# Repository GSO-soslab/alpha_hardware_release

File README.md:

## ALPHA HARDWARE RELEASE
This repository provides design files for ALPHA AUV hardware.
- `Electronics` folder contains KiCad PCB files, documentations and guides.
- `CAD` folder contains CAD files for the mechanical parts.

**License: CERN-OHL-S-2.0**

**Funding:** NSF Award #2221676, #2238168 and #2154901

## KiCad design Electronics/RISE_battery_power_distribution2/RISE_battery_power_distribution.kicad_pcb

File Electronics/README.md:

# ALPHA Hardware Repositority

The ALPHA Eletronics Hardware design is released under  [CERN-OHL-S-2.0](https://ohwr.org/cern_ohl_s_v2.txt) Licence
## **Introduction**

The most recent update:

- `sbc_hat` is a expansion board for single-board computers. It contains 8 RS232 ports (4 selectable between UART and RS232), 2 I2C buses, 2 ADC channels, and 5 direct GPIO connections. PDF schematics is available [here](https://github.com/GSO-soslab/alpha_hardware_release/blob/main/Electronics/doc/Schematics/sbc_hat.pdf)

- `thruster_driver` is a breakout board for MCU (MicroMod RP2040). This board is designed for interface with ESCs to control the thruster and servos. The voltage sensing capability is available (using a voltage devider) to monitoring the voltage to the thrusters. Communication ports are I2C, RS232 and RS485. Two additional GPIO is available for Digital Output fucntion. PDF schematics is available [here](https://github.com/GSO-soslab/alpha_hardware_release/blob/main/Electronics/doc/Schematics/thruster_driver.pdf)
 
- `Battery management` is a breakout board that uses diodes to allow battery pack parallization upto 4 packs. **IMPORTANT: You cannot charge batter packs from the Vout port on the board**

- `alpha_power_distribution_board` is a breakout board for distributing power sources for different devices on the ALPHA. You can plug in Pololu DC/DC circuit on the board with a 90 degree angled pin headers. A PDF schematics is available [here](https://github.com/GSO-soslab/alpha_hardware_release/blob/main/Electronics/doc/Schematics/alpha_power_distribution.pdf)

The detailed hardware information is available in the following links for users.
- [PI setup guide](https://github.com/GSO-soslab/alpha_hardware_release/blob/main/Electronics/doc/PI_setup_guide.md): This document provide information on how to configure the chips on the sbc_hat PBC.

- [`sbc_hat`](https://github.com/GSO-soslab/alpha_hardware_release/blob/main/Electronics/doc/SBC_HAT.md)

- [`thruster_driver`](https://github.com/GSO-soslab/alpha_hardware_release/blob/main/Electronics/doc/Thruster_driver.md)

- [`alpha_power_distribution_board`](https://github.com/GSO-soslab/alpha_hardware_release/blob/main/Electronics/doc/Alpha_power_distribution.md).

- [`Battery management`](https://github.com/GSO-soslab/alpha_hardware_release/blob/main/Electronics/doc/Battery_management.md)

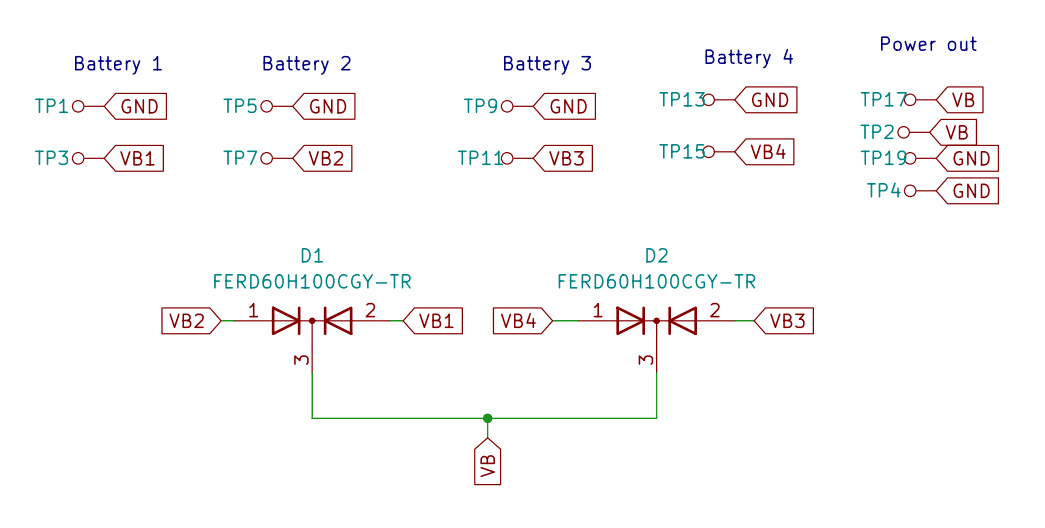
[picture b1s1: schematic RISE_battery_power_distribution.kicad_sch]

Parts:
D1, D2: FERD60H100CGY-TR; STPS41L60CG-TR
TP1, TP2, TP3, TP4, TP5, TP7, TP9, TP11, TP13, TP15, TP17, TP19: 5016; Test_Point_3.43x1.78mm; MPN 5016; Digi-Key_PN 36-5016CT-ND

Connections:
GND: TP1.1, TP4.1, TP5.1, TP9.1, TP13.1, TP19.1
VB: D1.3 (K), D2.3 (K), TP2.1, TP17.1
VB1: D1.2 (A), TP3.1
VB2: D1.1 (A), TP7.1
VB3: D2.2 (A), TP11.1
VB4: D2.1 (A), TP15.1

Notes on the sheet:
Battery 3
Battery 2
Battery 1
Battery 4
Power out

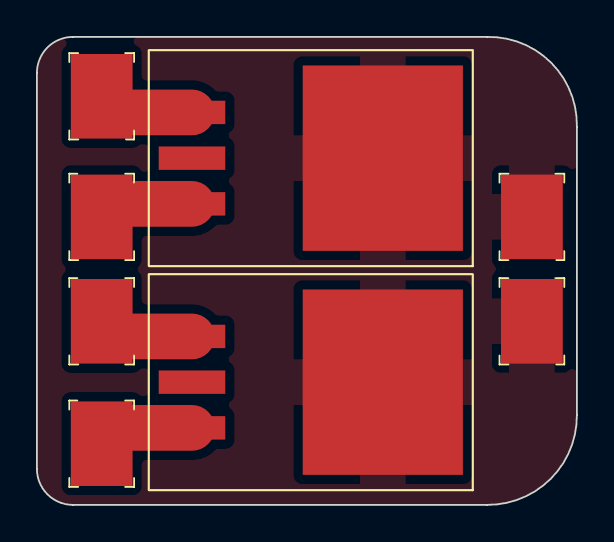
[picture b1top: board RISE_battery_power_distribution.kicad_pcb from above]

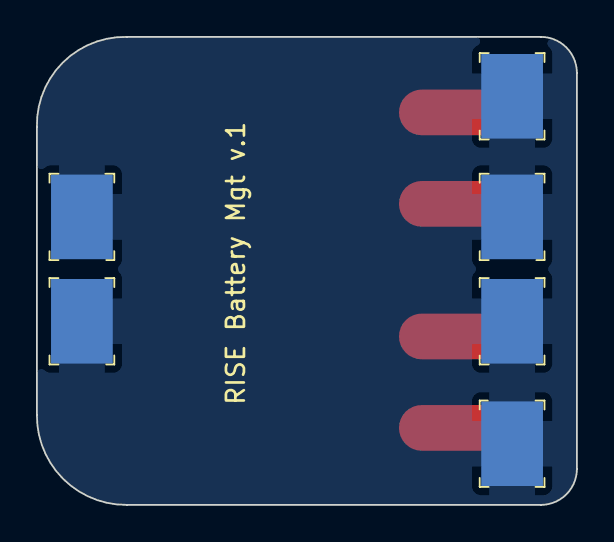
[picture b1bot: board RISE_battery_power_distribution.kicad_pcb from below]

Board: 2 copper layers, 30.0 x 26.0 mm, 14 parts (6 on the bottom side), 6 nets.

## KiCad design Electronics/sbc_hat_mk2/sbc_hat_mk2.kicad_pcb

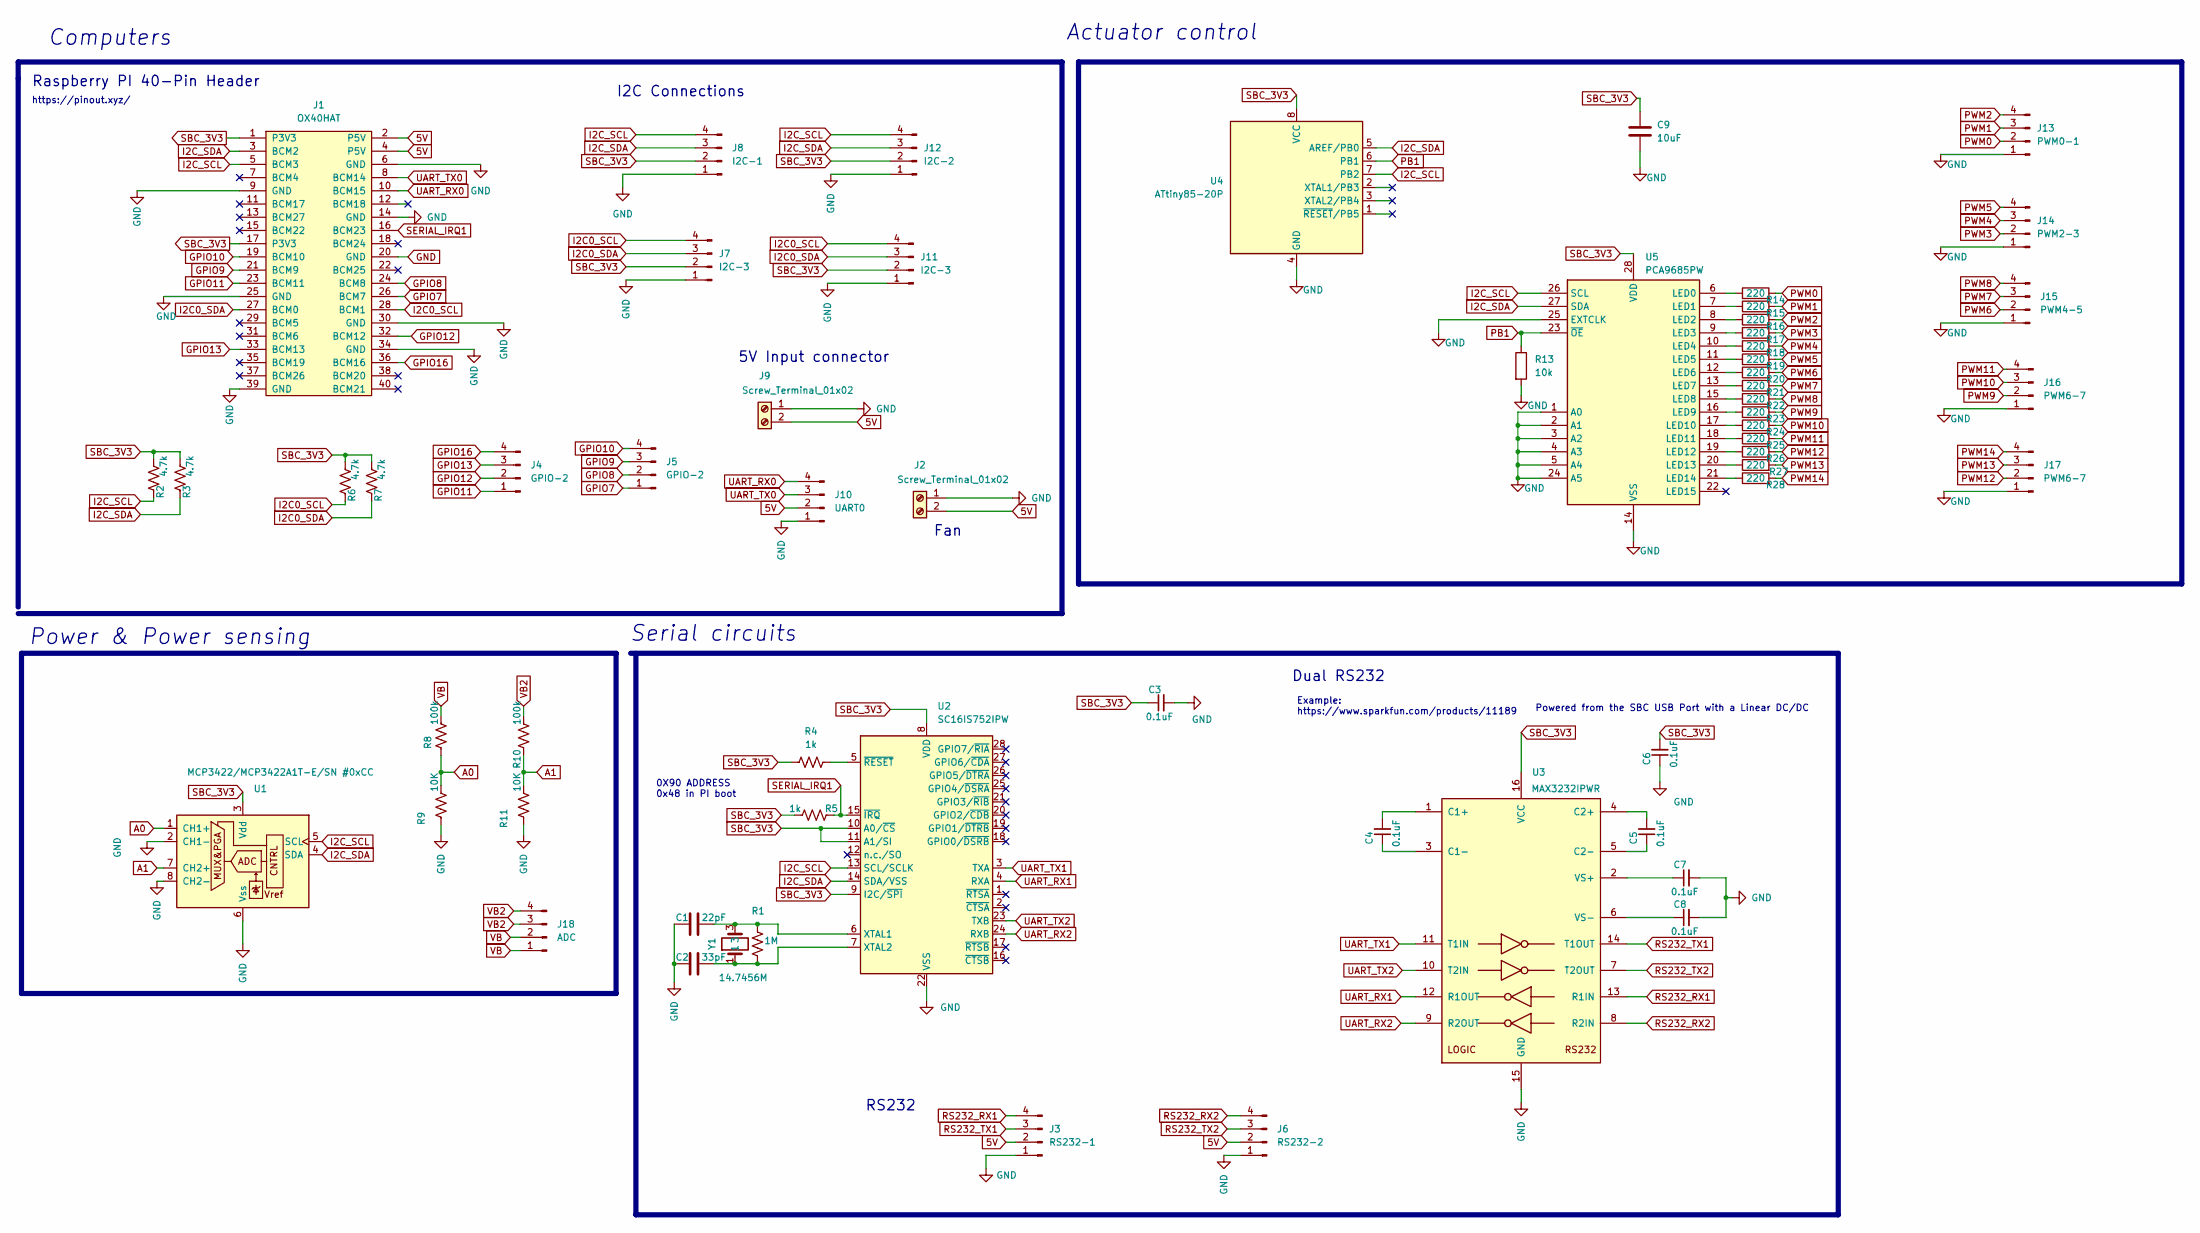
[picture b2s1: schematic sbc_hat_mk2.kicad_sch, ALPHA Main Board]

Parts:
C1: 22pF; C_0805_2012Metric; Manufacturer_Part_Number 08055J220FBTTR; Digikey Part Number 478-11911-1-ND
C2: 33pF; C_0805_2012Metric; Manufacturer_Part_Number 600F330FT250XT; Digikey Part Number 1284-1049-1-ND
C3, C4, C5, C6, C7, C8: 0.1uF; C_0805_2012Metric; Manufacturer_Part_Number 0805ZC104JAT2A; Digikey Part Number 478-11627-1-ND
C9: 10uF; C_0805_2012Metric
J1: OX40HAT; PinSocket_2x20_P2.54mm_Vertical; Mouser Part Number 474-PRT-14017
J2, J9: Screw_Terminal_01x02; TerminalBlock_Phoenix_MPT-0,5-2-2.54_1x02_P2.54mm_Horizontal; Manufacturer_Part_Number 1725656; Mouser Part Number 651-1725656
J3: RS232-1; JST_SH_BM04B-SRSS-TB_1x04-1MP_P1.00mm_Vertical; Manufacturer_Part_Number 4328; Digikey Part Number 1528-4328-ND
J4, J5: GPIO-2; JST_SH_BM04B-SRSS-TB_1x04-1MP_P1.00mm_Vertical; Manufacturer_Part_Number 4328; Digikey Part Number 1528-4328-ND
J6: RS232-2; JST_SH_BM04B-SRSS-TB_1x04-1MP_P1.00mm_Vertical; Manufacturer_Part_Number 4328; Digikey Part Number 1528-4328-ND
J7, J11: I2C-3; JST_SH_BM04B-SRSS-TB_1x04-1MP_P1.00mm_Vertical; Manufacturer_Part_Number 4328; Digikey Part Number 1528-4328-ND
J8: I2C-1; JST_SH_BM04B-SRSS-TB_1x04-1MP_P1.00mm_Vertical; Manufacturer_Part_Number 4328; Digikey Part Number 1528-4328-ND
J10: UART0; JST_SH_BM04B-SRSS-TB_1x04-1MP_P1.00mm_Vertical; Manufacturer_Part_Number 4328; Digikey Part Number 1528-4328-ND
J12: I2C-2; JST_SH_BM04B-SRSS-TB_1x04-1MP_P1.00mm_Vertical; Manufacturer_Part_Number 4328; Digikey Part Number 1528-4328-ND
J13: PWM0-1; JST_SH_BM04B-SRSS-TB_1x04-1MP_P1.00mm_Vertical; Manufacturer_Part_Number 4328; Digikey Part Number 1528-4328-ND
J14: PWM2-3; JST_SH_BM04B-SRSS-TB_1x04-1MP_P1.00mm_Vertical; Manufacturer_Part_Number 4328; Digikey Part Number 1528-4328-ND
J15: PWM4-5; JST_SH_BM04B-SRSS-TB_1x04-1MP_P1.00mm_Vertical; Manufacturer_Part_Number 4328; Digikey Part Number 1528-4328-ND
J16, J17: PWM6-7; JST_SH_BM04B-SRSS-TB_1x04-1MP_P1.00mm_Vertical; Manufacturer_Part_Number 4328; Digikey Part Number 1528-4328-ND
J18: ADC; JST_SH_BM04B-SRSS-TB_1x04-1MP_P1.00mm_Vertical; Manufacturer_Part_Number 4328; Digikey Part Number 1528-4328-ND
R1: 1M; R_0805_2012Metric; Manufacturer_Part_Number ERA-6AED105V; Mouser Part Number 667-ERA-6AED105V
R2, R3, R6, R7: 4.7k; R_0805_2012Metric; Manufacturer_Part_Number ERJ-T06J472V; Mouser Part Number 667-ERJ-T06J472V
R4, R5: 1k; R_0805_2012Metric; Manufacturer_Part_Number 1-2176092-8; Digikey Part Number A110543CT-ND
R8, R10: 100k; R_0805_2012Metric; Manufacturer_Part_Number ERA-6AEB104V; Mouser Part Number 667-ERA-6AEB104V
R9, R11: 10K; R_0805_2012Metric; Manufacturer_Part_Number ERA-6AEB104V; Mouser Part Number 667-ERA-6AEB104V
R13: 10k; R_0805_2012Metric
R14, R15, R16, R17, R18, R19, R20, R21, R22, R23, R24, R25, R26, R27, R28: 220; R_0805_2012Metric
U1: MCP3422/MCP3422A1T-E/SN #0xCC; SOIC-8-1EP_3.9x4.9mm_P1.27mm_EP2.29x3mm
U2: SC16IS752IPW; TSSOP-28_4.4x9.7mm_P0.65mm
U3: MAX3232IPWR; TSSOP-16_4.4x5mm_P0.65mm; Manufacturer_Part_Number MAX3232IPWR; Mouser Part Number 595-MAX3232IPWR
U4: ATtiny85-20P; DIP-8_W7.62mm
U5: PCA9685PW; TSSOP-28_4.4x9.7mm_P0.65mm
Y1: 14.7456M; Crystal_SMD_3225-4Pin_3.2x2.5mm

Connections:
5V: J1.2 (P5V), J1.4 (P5V), J2.2, J3.2, J6.2, J9.2, J10.2
A0: R8.2, R9.1, U1.1 (CH1+)
A1: R10.2, R11.1, U1.7 (CH2+)
GND: C1.1, C2.1, C3.2, C6.1, C7.2, C8.2, C9.2, J1.6 (GND), J1.9 (GND), J1.14 (GND), J1.20 (GND), J1.25 (GND), J1.30 (GND), J1.34 (GND), J1.39 (GND), J2.1, J3.1, J6.1, J7.1, J8.1, J9.1, J10.1, J11.1, J12.1, J13.1, J14.1, J15.1, J16.1, J17.1, R9.2, R11.2, R13.2, U1.2 (CH1-), U1.6 (Vss), U1.8 (CH2-), U2.22 (VSS), U3.15 (GND), U4.4 (GND), U5.1 (A0), U5.2 (A1), U5.3 (A2), U5.4 (A3), U5.5 (A4), U5.14 (VSS), U5.24 (A5), U5.25 (EXTCLK)
GPIO7: J1.26 (BCM7), J5.1
GPIO8: J1.24 (BCM8), J5.2
GPIO9: J1.21 (BCM9), J5.3
GPIO10: J1.19 (BCM10), J5.4
GPIO11: J1.23 (BCM11), J4.1
GPIO12: J1.32 (BCM12), J4.2
GPIO13: J1.33 (BCM13), J4.3
GPIO16: J1.36 (BCM16), J4.4
I2C0_SCL: J1.28 (BCM1), J7.4, J11.4, R6.1
I2C0_SDA: J1.27 (BCM0), J7.3, J11.3, R7.1
I2C_SCL: J1.5 (BCM3), J8.4, J12.4, R2.1, U1.5 (SCL), U2.13 (SCL/SCLK), U4.7 (PB2), U5.26 (SCL)
I2C_SDA: J1.3 (BCM2), J8.3, J12.3, R3.1, U1.4 (SDA), U2.14 (SDA/VSS), U4.5 (AREF/PB0), U5.27 (SDA)
unnamed: C1.2, R1.1, U2.6 (XTAL1), Y1.3
unnamed: C2.2, R1.2, U2.7 (XTAL2), Y1.1
unnamed: R4.2, U2.5 (~RESET)
unnamed: C4.2, U3.1 (C1+)
unnamed: C4.1, U3.3 (C1-)
unnamed: C5.2, U3.4 (C2+)
unnamed: C5.1, U3.5 (C2-)
unnamed: C7.1, U3.2 (VS+)
unnamed: C8.1, U3.6 (VS-)
unnamed: R14.1, U5.6 (LED0)
unnamed: R15.1, U5.7 (LED1)
unnamed: R16.1, U5.8 (LED2)
unnamed: R17.1, U5.9 (LED3)
unnamed: R18.1, U5.10 (LED4)
unnamed: R19.1, U5.11 (LED5)
unnamed: R20.1, U5.12 (LED6)
unnamed: R21.1, U5.13 (LED7)
unnamed: R22.1, U5.15 (LED8)
unnamed: R23.1, U5.16 (LED9)
unnamed: R24.1, U5.17 (LED10)
unnamed: R25.1, U5.18 (LED11)
unnamed: R26.1, U5.19 (LED12)
unnamed: R27.1, U5.20 (LED13)
unnamed: R28.1, U5.21 (LED14)
PB1: R13.1, U4.6 (PB1), U5.23 (~OE)
PWM0: J13.2, R14.2
PWM1: J13.3, R15.2
PWM2: J13.4, R16.2
PWM3: J14.2, R17.2
PWM4: J14.3, R18.2
PWM5: J14.4, R19.2
PWM6: J15.2, R20.2
PWM7: J15.3, R21.2
PWM8: J15.4, R22.2
PWM9: J16.2, R23.2
PWM10: J16.3, R24.2
PWM11: J16.4, R25.2
PWM12: J17.2, R26.2
PWM13: J17.3, R27.2
PWM14: J17.4, R28.2
RS232_RX1: J3.4, U3.13 (R1IN)
RS232_RX2: J6.4, U3.8 (R2IN)
RS232_TX1: J3.3, U3.14 (T1OUT)
RS232_TX2: J6.3, U3.7 (T2OUT)
SBC_3V3: C3.1, C6.2, C9.1, J1.1 (P3V3), J1.17 (P3V3), J7.2, J8.2, J11.2, J12.2, R2.2, R3.2, R4.1, R5.2, R6.2, R7.2, U1.3 (Vdd), U2.8 (VDD), U2.9 (I2C/~SPI), U2.10 (A0/~CS), U2.11 (A1/SI), U3.16 (VCC), U4.8 (VCC), U5.28 (VDD)
SERIAL_IRQ1: J1.16 (BCM23), R5.1, U2.15 (~IRQ)
UART_RX0: J1.10 (BCM15), J10.4
UART_RX1: U2.4 (RXA), U3.12 (R1OUT)
UART_RX2: U2.24 (RXB), U3.9 (R2OUT)
UART_TX0: J1.8 (BCM14), J10.3
UART_TX1: U2.3 (TXA), U3.11 (T1IN)
UART_TX2: U2.23 (TXB), U3.10 (T2IN)
VB: J18.1, J18.2, R8.1
VB2: J18.3, J18.4, R10.1

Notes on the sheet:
I2C Connections
0X90 ADDRESS 0x48 in PI boot
5V Input connector
RS232
Serial circuits
Dual RS232
Power & Power sensing
Example: https://www.sparkfun.com/products/11189
Fan
Computers
https://pinout.xyz/
Actuator control
Raspberry PI 40-Pin Header
Powered from the SBC USB Port with a Linear DC/DC

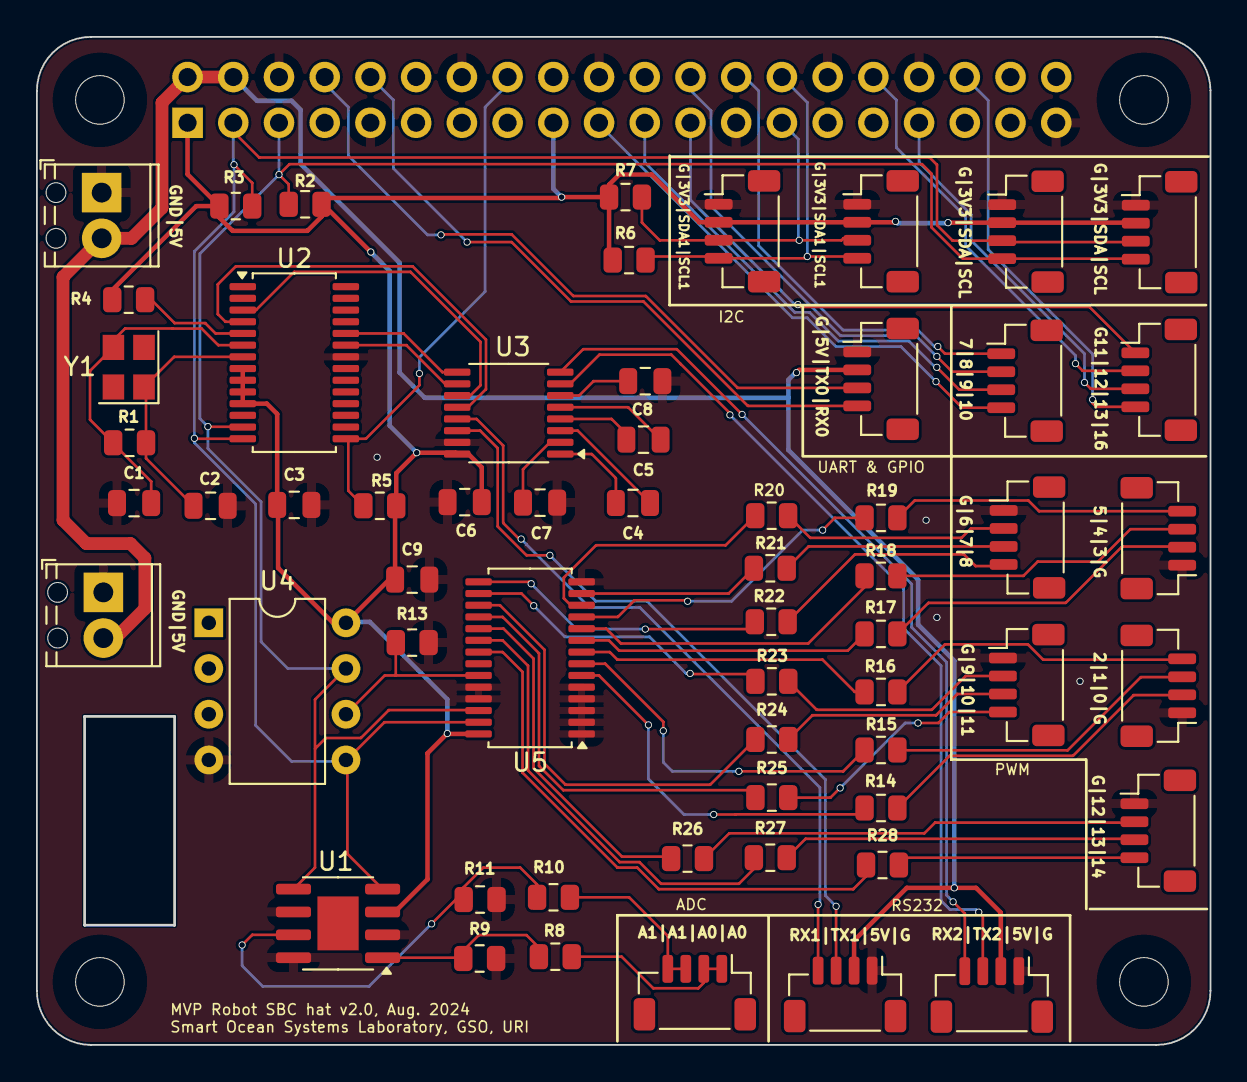
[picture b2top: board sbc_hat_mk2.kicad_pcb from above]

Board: 2 copper layers, 65.2 x 56.0 mm, 64 parts (1 on the bottom side), 70 nets.

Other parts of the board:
MH1, MH2, MH3, MH4: MountingHole_2.7mm_M2.5

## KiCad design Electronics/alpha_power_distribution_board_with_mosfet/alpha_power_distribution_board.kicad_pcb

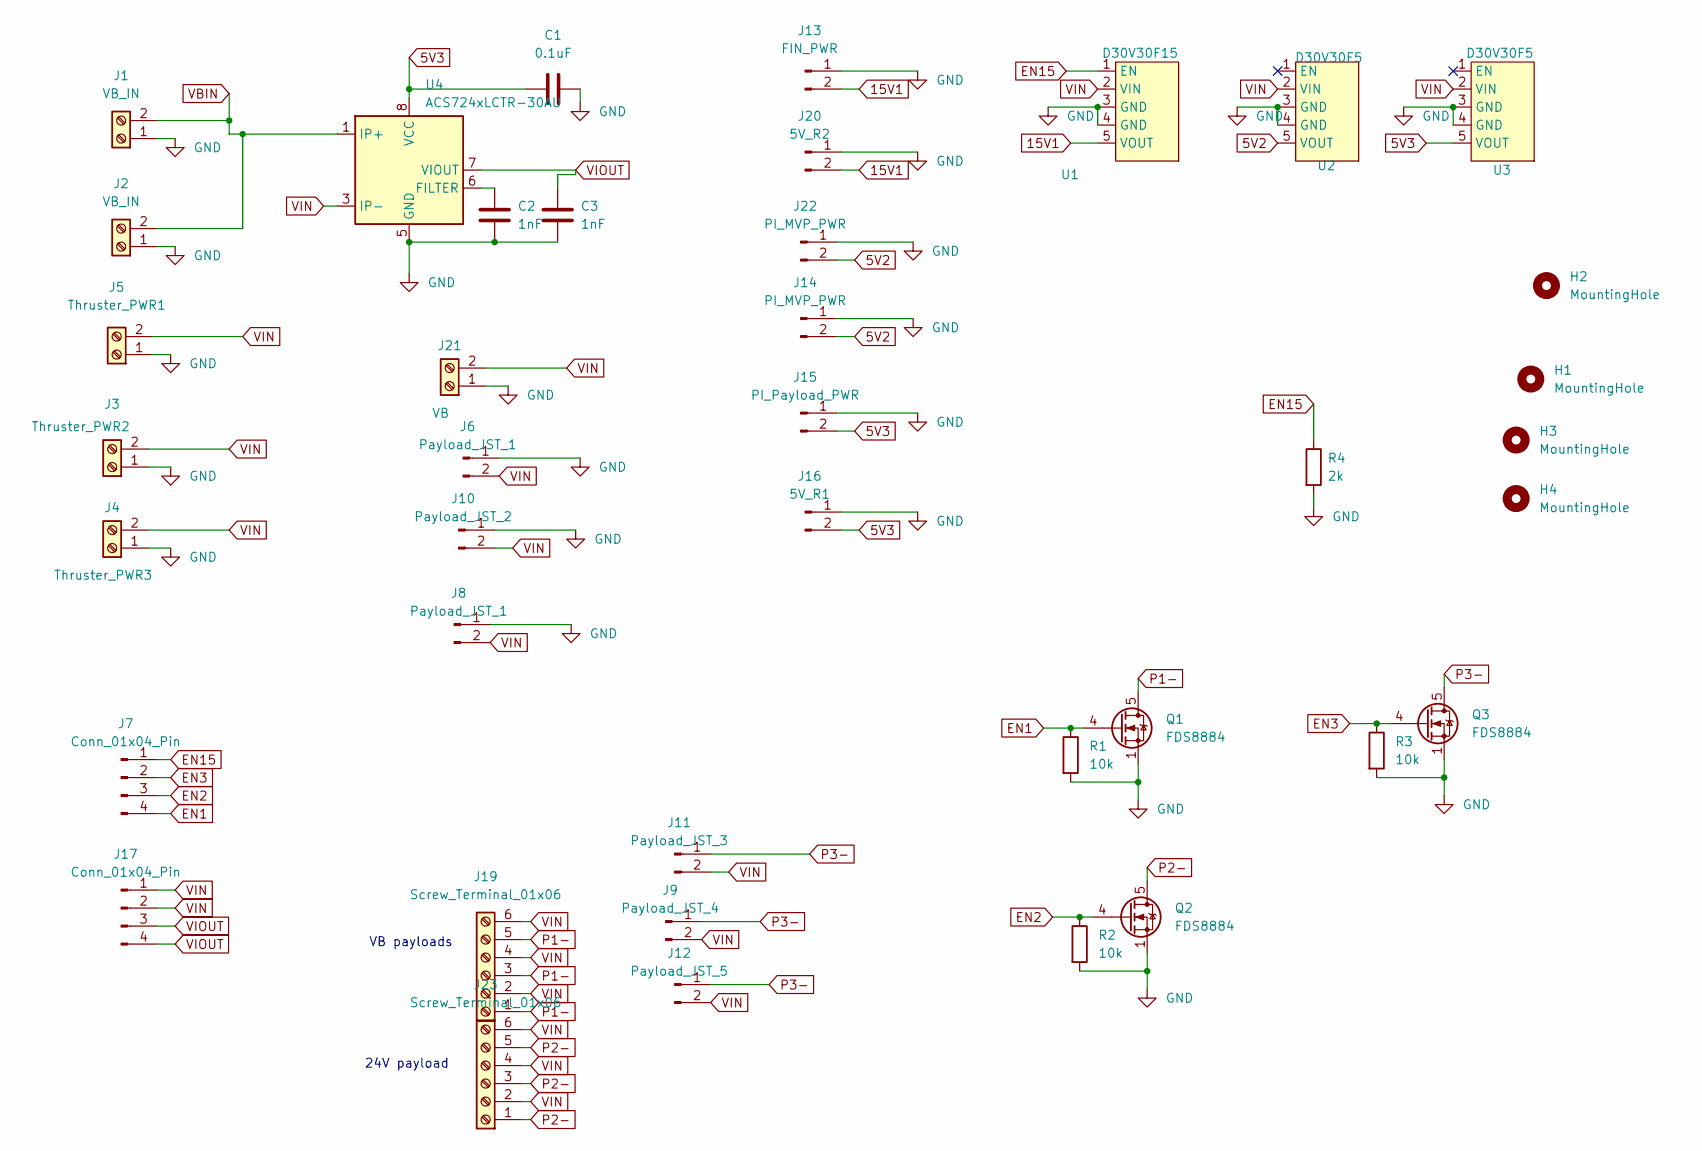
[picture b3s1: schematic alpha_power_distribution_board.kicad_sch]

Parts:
C1: 0.1uF; C_0805_2012Metric
C2, C3: 1nF; C_0805_2012Metric
H1, H2, H3, H4: MountingHole; MountingHole_2.7mm_M2.5
J1, J2: VB_IN; Pololu_5mm
J3: Thruster_PWR2; Pololu_5mm
J4: Thruster_PWR3; Pololu_5mm
J5: Thruster_PWR1; Pololu_5mm
J6, J8: Payload_JST_1; JST_XH_B2B-XH-A_1x02_P2.50mm_Vertical
J7, J17: Conn_01x04_Pin; JST_SH_BM04B-SRSS-TB_1x04-1MP_P1.00mm_Vertical
J9: Payload_JST_4; JST_XH_B02B-XH-A_02x2.50mm_Straight
J10: Payload_JST_2; JST_XH_B02B-XH-A_02x2.50mm_Straight
J11: Payload_JST_3; JST_XH_B02B-XH-A_02x2.50mm_Straight
J12: Payload_JST_5; JST_XH_B02B-XH-A_02x2.50mm_Straight
J13: FIN_PWR; JST_XH_B02B-XH-A_02x2.50mm_Straight
J14, J22: PI_MVP_PWR; JST_XH_B02B-XH-A_02x2.50mm_Straight
J15: PI_Payload_PWR; JST_XH_B02B-XH-A_02x2.50mm_Straight
J16: 5V_R1; JST_XH_B02B-XH-A_02x2.50mm_Straight
J19, J23: Screw_Terminal_01x06; TerminalBlock_TE_282834-6_1x06_P2.54mm_Horizontal
J20: 5V_R2; JST_XH_B02B-XH-A_02x2.50mm_Straight
J21: VB; Pololu_5mm
Q1, Q2, Q3: FDS8884; SOIC-8_3.9x4.9mm_P1.27mm
R1, R2, R3: 10k; R_0805_2012Metric
R4: 2k; R_0805_2012Metric
U1: D30V30F15; D36V28F5
U2, U3: D30V30F5; D36V28F5
U4: ACS724xLCTR-30AU; SOIC-8_3.9x4.9mm_P1.27mm

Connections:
5V2: J14.2, J22.2, U2.5 (VOUT)
5V3: C1.1, J15.2, J16.2, U3.5 (VOUT), U4.8 (VCC)
15V1: J13.2, J20.2, U1.5 (VOUT)
EN1: J7.4, Q1.4 (G), R1.1
EN2: J7.3, Q2.4 (G), R2.1
EN3: J7.2, Q3.4 (G), R3.1
EN15: J7.1, R4.1, U1.1 (EN)
GND: C1.2, C2.1, C3.1, J1.1, J2.1, J3.1, J4.1, J5.1, J6.1, J8.1, J10.1, J13.1, J14.1, J15.1, J16.1, J20.1, J21.1, J22.1, Q1.1 (S), Q1.2 (S), Q1.3 (S), Q2.1 (S), Q2.2 (S), Q2.3 (S), Q3.1 (S), Q3.2 (S), Q3.3 (S), R1.2, R2.2, R3.2, R4.2, U1.3 (GND), U1.4 (GND), U2.3 (GND), U2.4 (GND), U3.3 (GND), U3.4 (GND), U4.5 (GND)
unnamed: C2.2, U4.6 (FILTER)
P1-: J19.1, J19.3, J19.5, Q1.5 (D), Q1.6 (D), Q1.7 (D), Q1.8 (D)
P2-: J23.1, J23.3, J23.5, Q2.5 (D), Q2.6 (D), Q2.7 (D), Q2.8 (D)
P3-: J9.1, J11.1, J12.1, Q3.5 (D), Q3.6 (D), Q3.7 (D), Q3.8 (D)
VBIN: J1.2, J2.2, U4.1 (IP+), U4.2 (IP+)
VIN: J3.2, J4.2, J5.2, J6.2, J8.2, J9.2, J10.2, J11.2, J12.2, J17.1, J17.2, J19.2, J19.4, J19.6, J21.2, J23.2, J23.4, J23.6, U1.2 (VIN), U2.2 (VIN), U3.2 (VIN), U4.3 (IP-), U4.4 (IP-)
VIOUT: C3.2, J17.3, J17.4, U4.7 (VIOUT)

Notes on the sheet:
VB payloads
24V payload

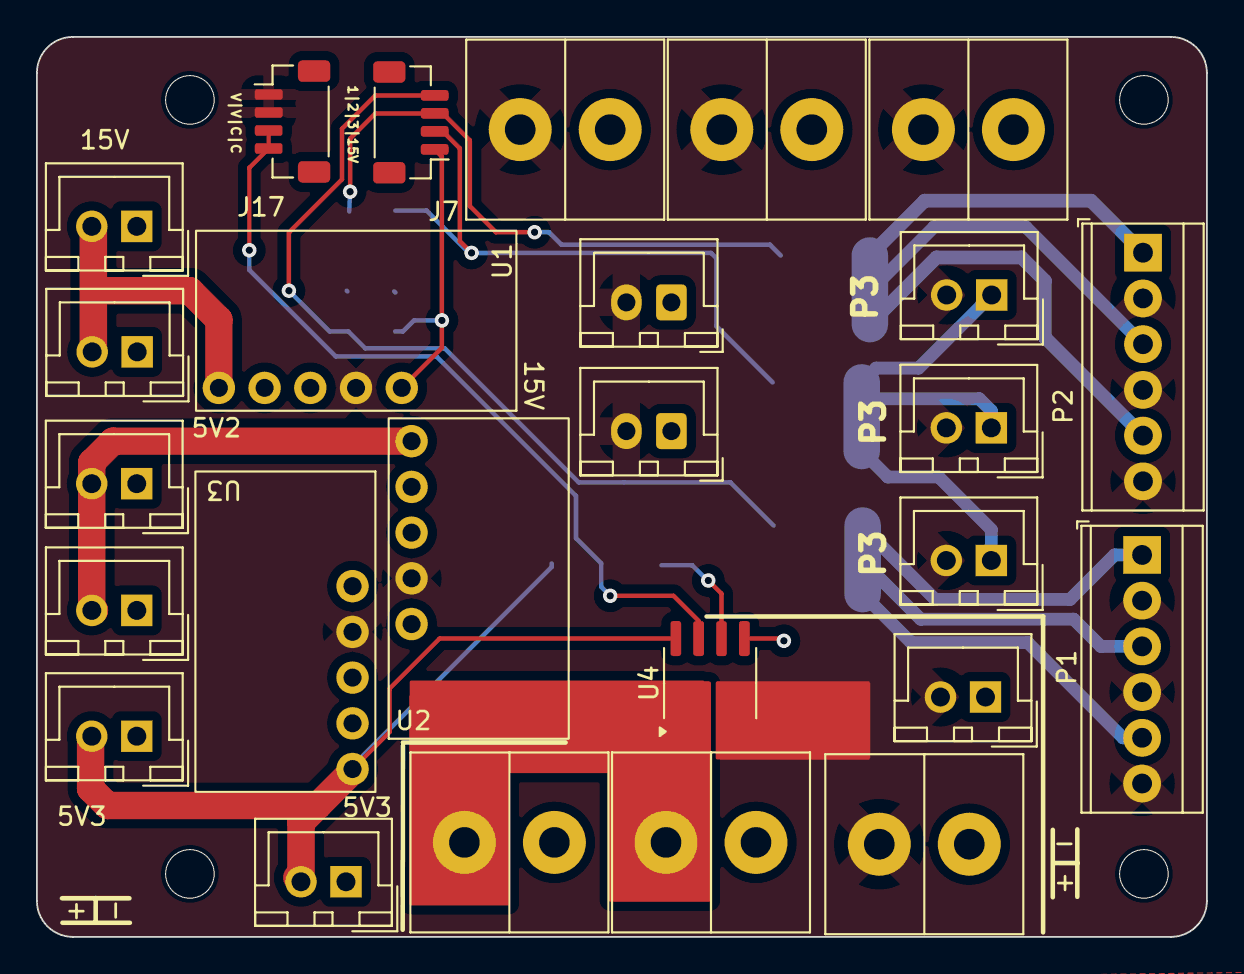
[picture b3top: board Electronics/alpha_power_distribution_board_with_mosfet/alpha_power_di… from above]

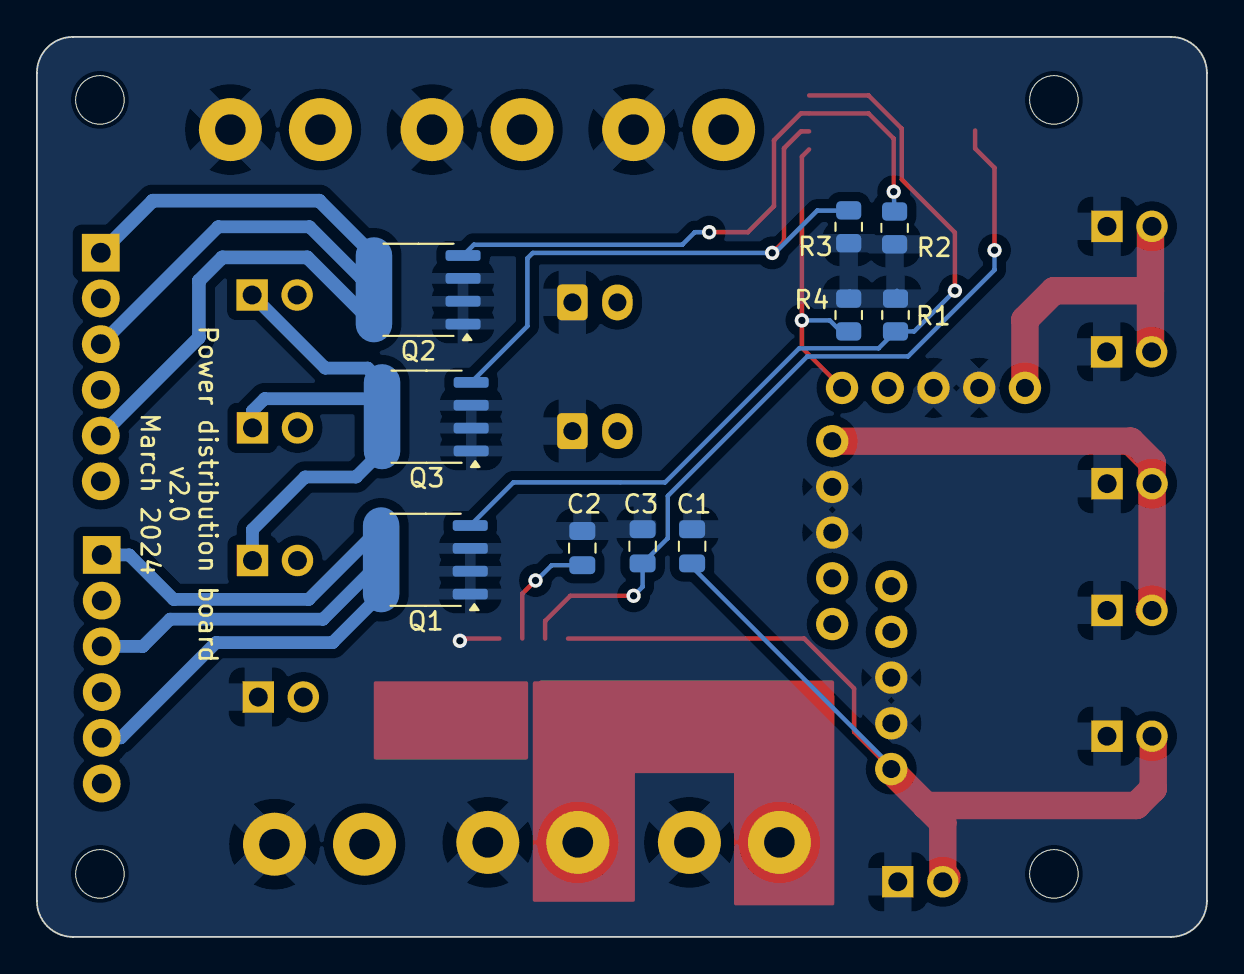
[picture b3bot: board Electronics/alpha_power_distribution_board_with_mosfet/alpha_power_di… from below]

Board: 2 copper layers, 65.0 x 50.0 mm, 40 parts (10 on the bottom side), 15 nets.

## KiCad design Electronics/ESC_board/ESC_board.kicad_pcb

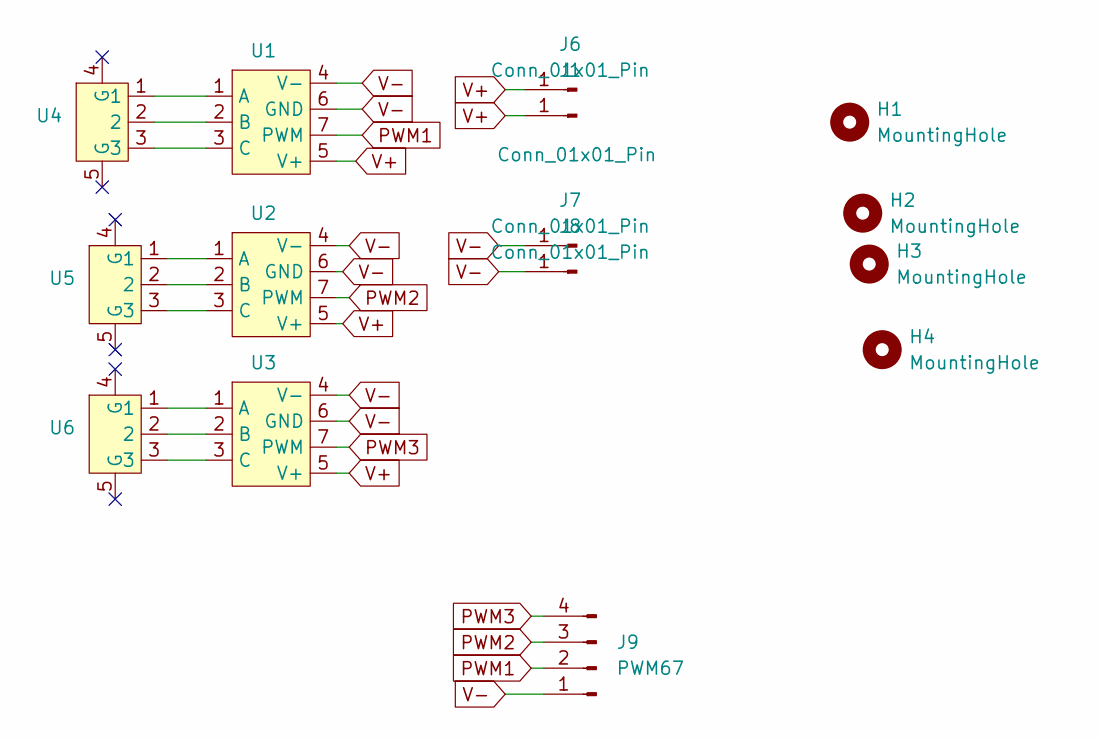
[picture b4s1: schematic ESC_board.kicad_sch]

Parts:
H1, H2, H3, H4: MountingHole; MountingHole_2.5mm_Pad
J1, J6, J7, J8: Conn_01x01_Pin; TestPoint_Loop_D3.80mm_Drill2.0mm
J9: PWM67; JST_SH_BM04B-SRSS-TB_1x04-1MP_P1.00mm_Vertical; Manufacturer_Part_Number 4328; Digikey Part Number 1528-4328-ND
U1, U2, U3: BR_ESC
U4, U5, U6: AMASS_MR30PW-FB_1x03_P3.50mm_Horizontal

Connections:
unnamed: U1.1 (A), U4.1
unnamed: U1.2 (B), U4.2
unnamed: U1.3 (C), U4.3
unnamed: U2.1 (A), U5.1
unnamed: U2.2 (B), U5.2
unnamed: U2.3 (C), U5.3
unnamed: U3.1 (A), U6.1
unnamed: U3.2 (B), U6.2
unnamed: U3.3 (C), U6.3
PWM1: J9.2, U1.7 (PWM)
PWM2: J9.3, U2.7 (PWM)
PWM3: J9.4, U3.7 (PWM)
V+: J1.1, J6.1, U1.5 (V+), U2.5 (V+), U3.5 (V+)
V-: J7.1, J8.1, J9.1, U1.4 (V-), U1.6 (GND), U2.4 (V-), U2.6 (GND), U3.4 (V-), U3.6 (GND)

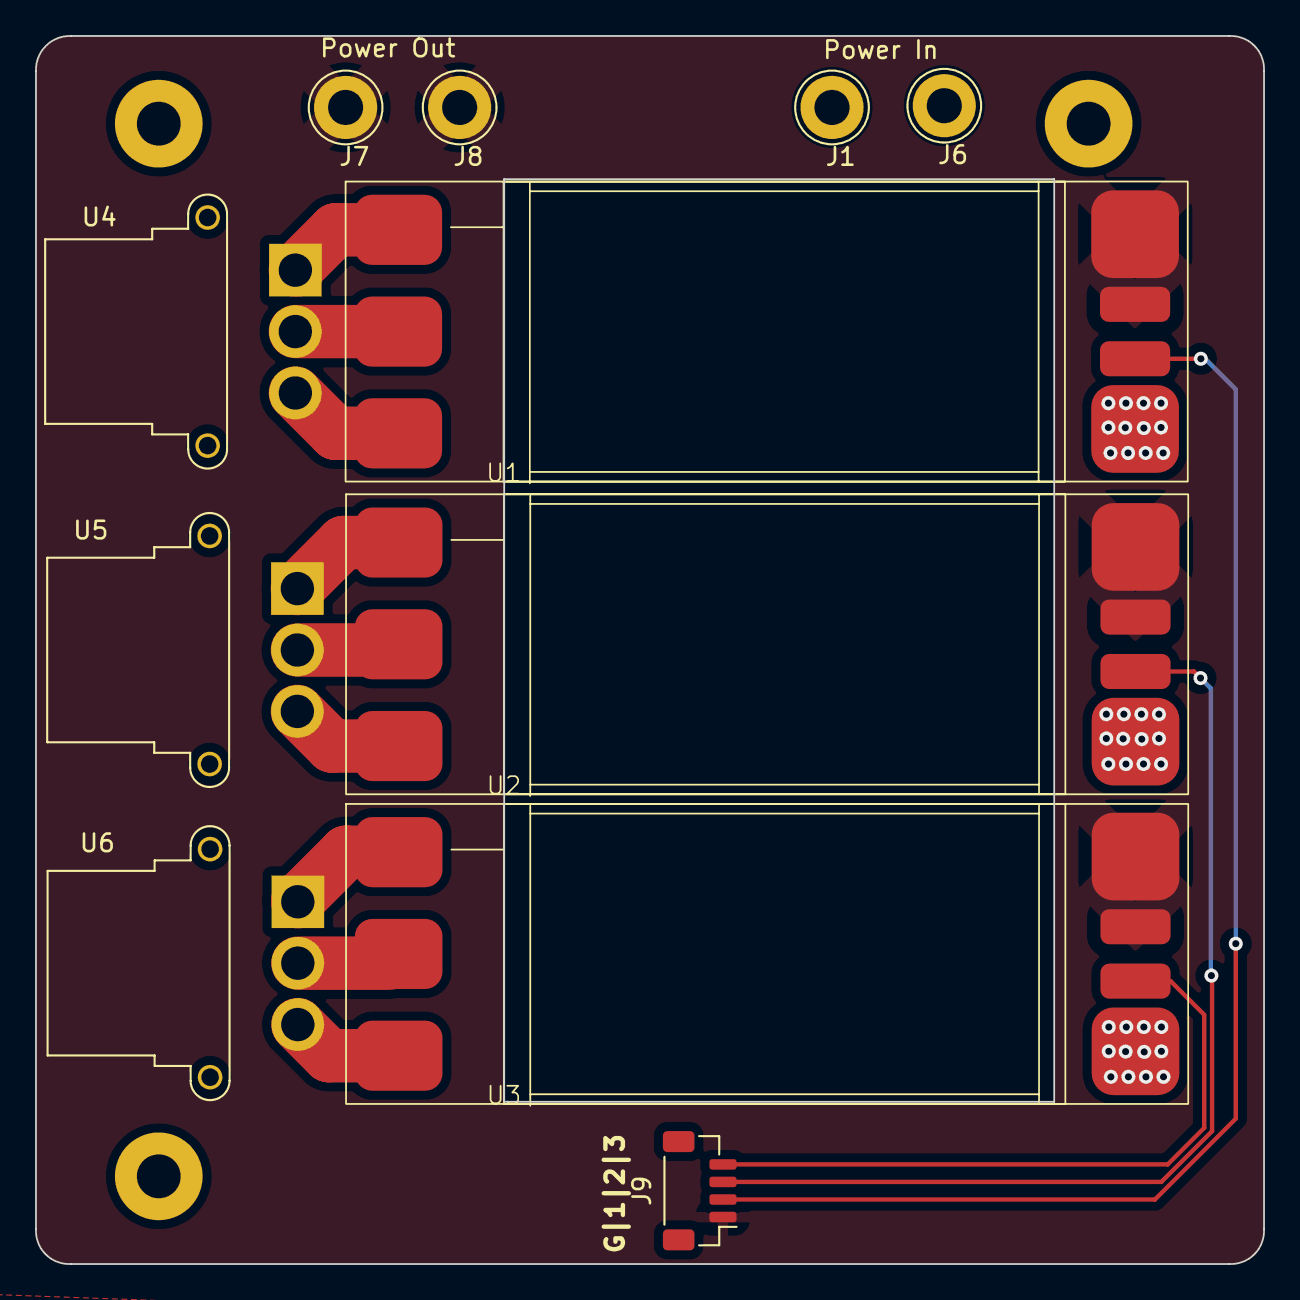
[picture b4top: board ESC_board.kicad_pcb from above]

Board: 2 copper layers, 70.0 x 70.0 mm, 14 parts (0 on the bottom side), 14 nets.

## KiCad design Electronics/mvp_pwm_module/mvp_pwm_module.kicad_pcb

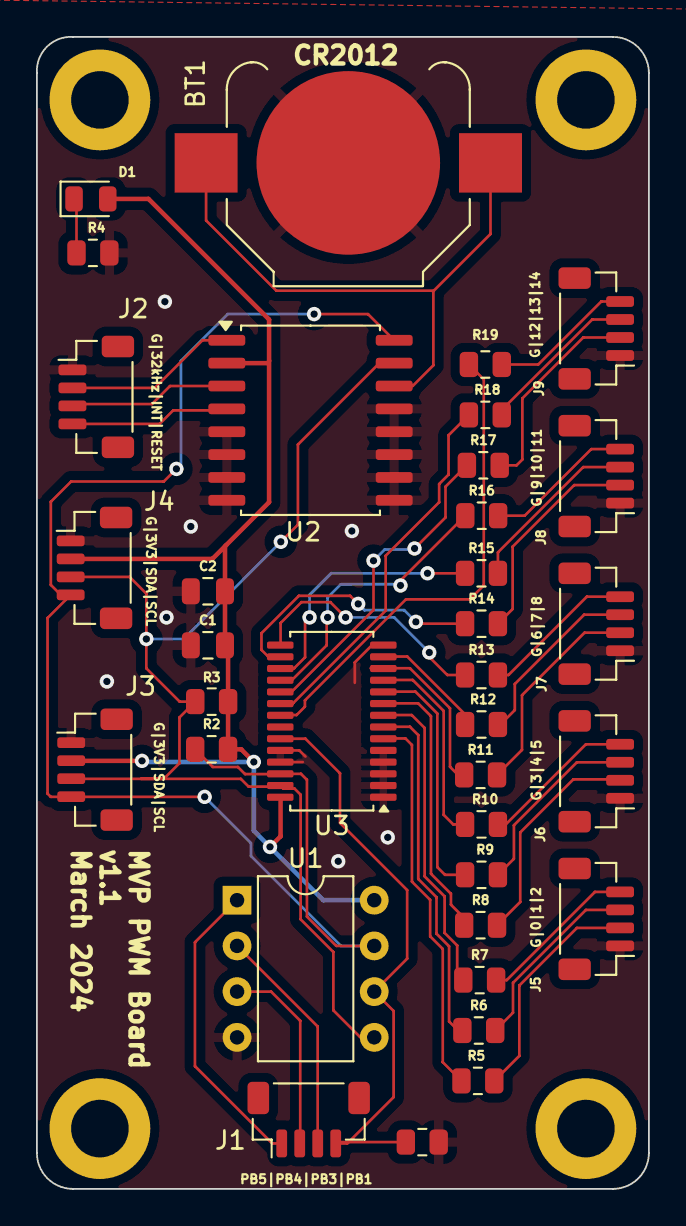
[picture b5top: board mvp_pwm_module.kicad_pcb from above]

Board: 2 copper layers, 34.0 x 64.0 mm, 39 parts (0 on the bottom side), 43 nets.

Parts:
BT1: Battery_Cell; BatteryHolder_Keystone_3000_1x12mm
C1, C2: 10uF; C_0805_2012Metric
D1: LED; LED_0805_2012Metric
H1, H2, H3, H4: MountingHole; MountingHole_3.2mm_M3_DIN965_Pad
J1, J2: GPIO; JST_SH_BM04B-SRSS-TB_1x04-1MP_P1.00mm_Vertical
J3, J4: I2C; JST_SH_BM04B-SRSS-TB_1x04-1MP_P1.00mm_Vertical
J5: PWM0-1; JST_SH_BM04B-SRSS-TB_1x04-1MP_P1.00mm_Vertical
J6: PWM2-3; JST_SH_BM04B-SRSS-TB_1x04-1MP_P1.00mm_Vertical
J7: PWM4-5; JST_SH_BM04B-SRSS-TB_1x04-1MP_P1.00mm_Vertical
J8, J9: PWM6-7; JST_SH_BM04B-SRSS-TB_1x04-1MP_P1.00mm_Vertical
R1, R2, R3: 10k; R_0805_2012Metric
R4, R5, R6, R7, R8, R9, R10, R11, R12, R13, R14, R15, R16, R17, R18, R19: 220; R_0805_2012Metric
U1: ATtiny85-20P; DIP-8_W7.62mm
U2: DS3231M; SOIC-16W_7.5x10.3mm_P1.27mm
U3: PCA9685PW; TSSOP-28_4.4x9.7mm_P0.65mm

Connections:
3V3: C1.1, C2.1, D1.2 (A), J3.2, J4.2, R2.1, R3.1, U1.8 (VCC), U2.2 (VCC), U3.28 (VDD)
32KHz: J2.2, U2.1 (32KHZ)
GND: BT1.2 (-), C1.2, C2.2, J2.1, J3.1, J4.1, J5.1, J6.1, J7.1, J8.1, J9.1, R1.2, R4.2, U1.4 (GND), U2.5 (GND), U2.6 (GND), U2.7 (GND), U2.8 (GND), U2.9 (GND), U2.10 (GND), U2.11 (GND), U2.12 (GND), U2.13 (GND), U3.1 (A0), U3.2 (A1), U3.3 (A2), U3.4 (A3), U3.5 (A4), U3.14 (VSS), U3.24 (A5), U3.25 (EXTCLK)
I2C_SCL: J3.4, J4.4, R2.2, U1.7 (PB2), U2.16 (SCL), U3.26 (SCL)
I2C_SDA: J3.3, J4.3, R3.2, U1.5 (AREF/PB0), U2.15 (SDA), U3.27 (SDA)
INT_SQW: J2.3, U2.3 (~INT/SQW)
unnamed: BT1.1 (+), U2.14 (VBAT)
unnamed: D1.1 (K), R4.1
unnamed: R5.1, U3.6 (LED0)
unnamed: R6.1, U3.7 (LED1)
unnamed: R7.1, U3.8 (LED2)
unnamed: R8.1, U3.9 (LED3)
unnamed: R9.1, U3.10 (LED4)
unnamed: R10.1, U3.11 (LED5)
unnamed: R11.1, U3.12 (LED6)
unnamed: R12.1, U3.13 (LED7)
unnamed: R13.1, U3.15 (LED8)
unnamed: R14.1, U3.16 (LED9)
unnamed: R15.1, U3.17 (LED10)
unnamed: R16.1, U3.18 (LED11)
unnamed: R17.1, U3.19 (LED12)
unnamed: R18.1, U3.20 (LED13)
unnamed: R19.1, U3.21 (LED14)
PB1: J1.4, R1.1, U1.6 (PB1), U3.23 (~OE)
PB3: J1.3, U1.2 (XTAL1/PB3)
PB4: J1.2, U1.3 (XTAL2/PB4)
PB5: J1.1, U1.1 (~RESET/PB5)
PWM0: J5.2, R5.2
PWM1: J5.3, R6.2
PWM2: J5.4, R7.2
PWM3: J6.2, R8.2
PWM4: J6.3, R9.2
PWM5: J6.4, R10.2
PWM6: J7.2, R11.2
PWM7: J7.3, R12.2
PWM8: J7.4, R13.2
PWM9: J8.2, R14.2
PWM10: J8.3, R15.2
PWM11: J8.4, R16.2
PWM12: J9.2, R17.2
PWM13: J9.3, R18.2
PWM14: J9.4, R19.2
RTC_RESET: J2.4, U2.4 (~RST)
